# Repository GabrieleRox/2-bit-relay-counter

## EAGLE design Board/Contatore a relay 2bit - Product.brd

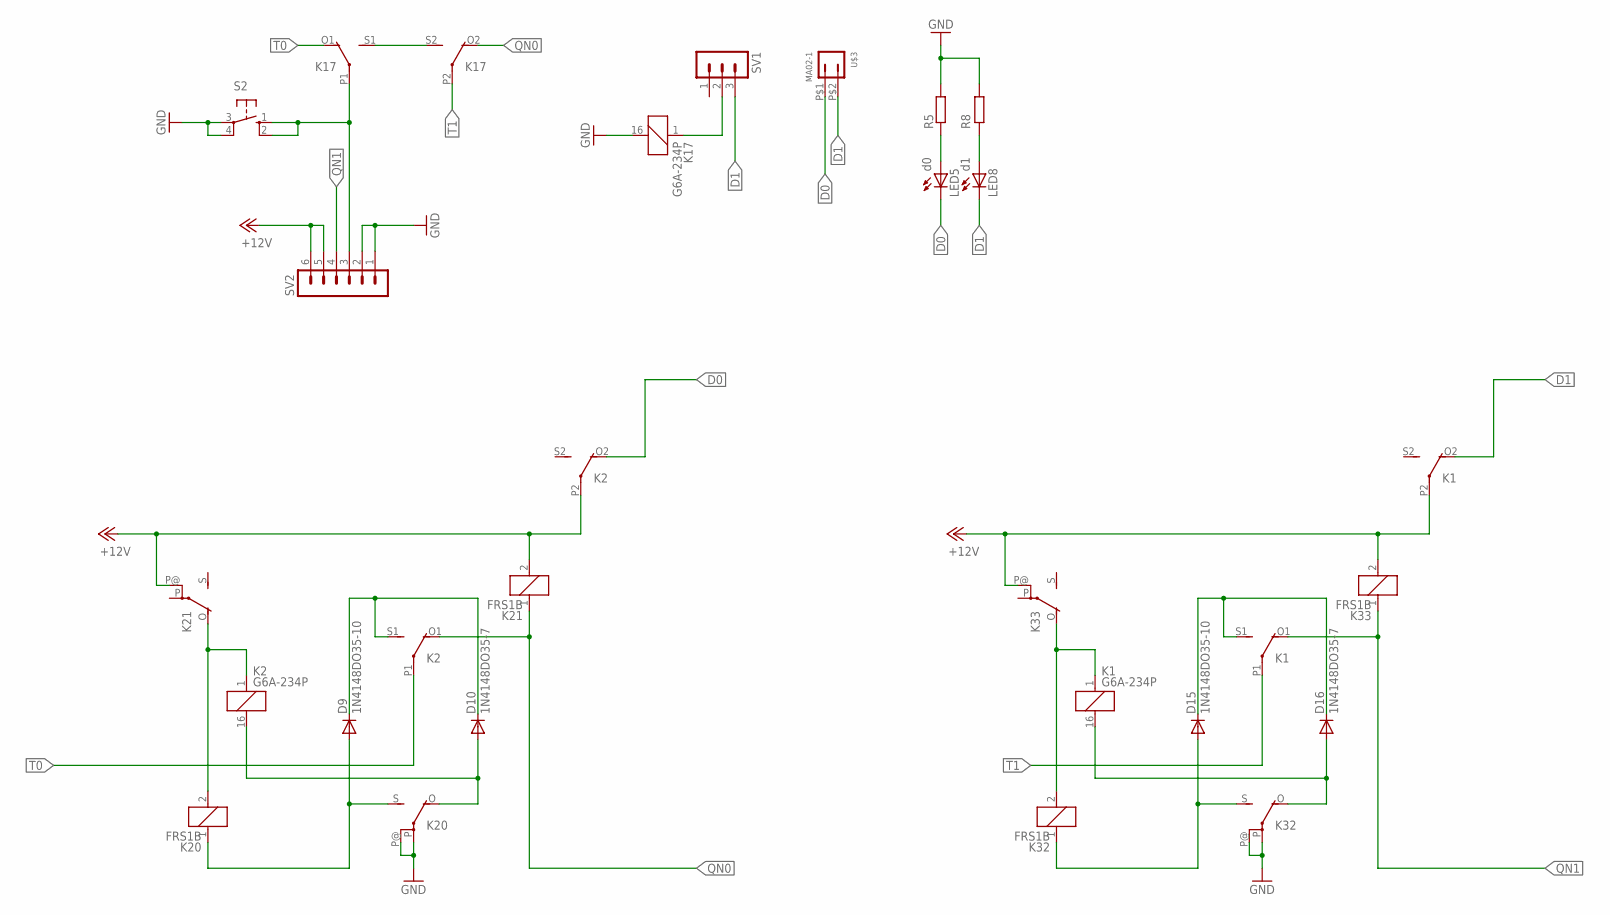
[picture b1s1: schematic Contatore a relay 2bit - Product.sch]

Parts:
D9, D15: 1N4148DO35-10; DO35-10
D10, D16: 1N4148DO35-7; DO35-7
K1, K2, K17: G6A-234P
K20, K21, K32, K33: FRS1B
LED5: d0; LED3MM
LED8: d1; LED3MM
R5, R8: R-EU_M0805; M0805
S2: 10-XX; B3F-10XX
SV1: MA03-1
SV2: MA06-1
U$3: MA02-1

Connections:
+12V: K1.P2, K2.P2, K21.2, K21.P@, K33.2, K33.P@, SV2.5, SV2.6
D0: K2.O2 (O), LED5.K (C), U$3.P$1 (1)
D1: K1.O2 (O), LED8.K (C), SV1.3, U$3.P$2 (2)
GND: K17.16 (2), K20.P, K20.P@, K32.P, K32.P@, R5.2, R8.2, S2.3, S2.4 (P1), SV2.1, SV2.2
unnamed: K17.1, SV1.2
unnamed: K17.P1, S2.1 (S), S2.2 (S1), SV2.3
unnamed: D10.A, K2.16 (2), K20.O
unnamed: D9.A, K20.1, K20.S
unnamed: K2.1, K20.2, K21.O
unnamed: D9.C, D10.C, K2.S1 (S)
unnamed: D16.A, K1.16 (2), K32.O
unnamed: D15.A, K32.1, K32.S
unnamed: K1.1, K32.2, K33.O
unnamed: D15.C, D16.C, K1.S1 (S)
unnamed: K17.S1 (S), K17.S2 (S)
unnamed: LED5.A, R5.1
unnamed: LED8.A, R8.1
QN0: K2.O1 (O), K17.O2 (O), K21.1
QN1: K1.O1 (O), K33.1, SV2.4
T0: K2.P1, K17.O1 (O)
T1: K1.P1, K17.P2

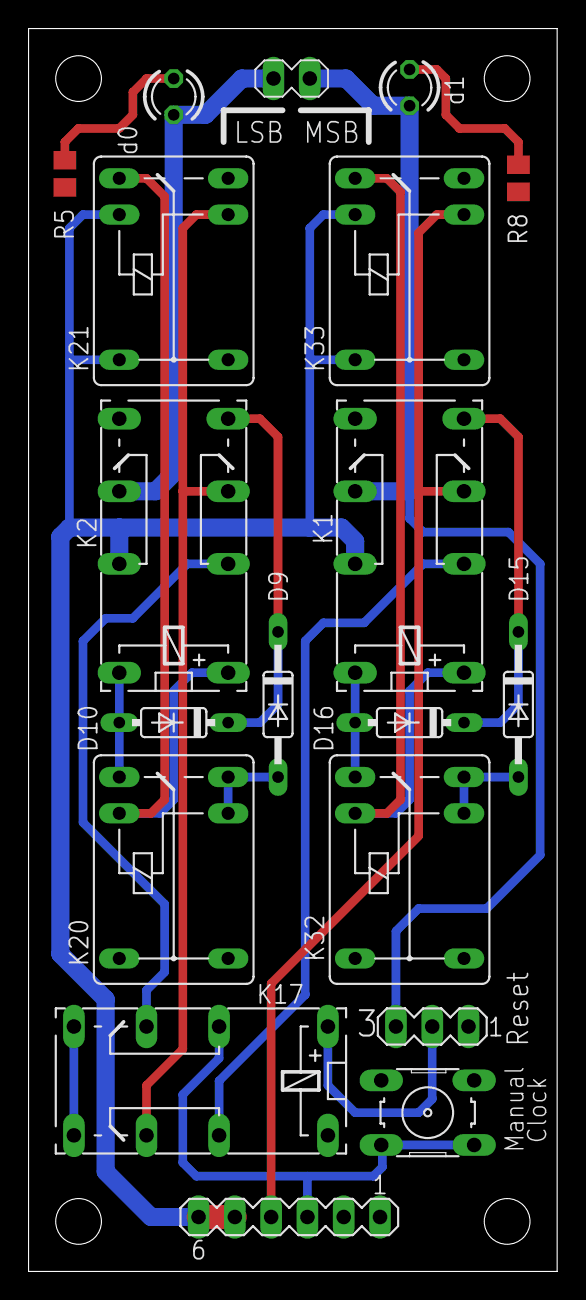
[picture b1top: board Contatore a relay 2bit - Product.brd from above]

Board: 2 copper layers, 37.0 x 87.0 mm, 19 parts (0 on the bottom side), 21 nets.

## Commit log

2022-02-11 First Upload
